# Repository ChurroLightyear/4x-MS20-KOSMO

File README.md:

# 4x MS20 KOSMO (ROUGH DRAFT)
This is a stackable but very crude MS20 filter based on the KS20 by Kassutronics

This has been tested and is working with some 100% neccesary changes

***The transitor footprints ended up backwords on Kicad.

Theres a few changes that are planned with this filter but it's up and working great atm. Everything is offboard wired from the PCBs. I drilled a custom alumunum panel and made some changes to the circuit.

The biggest change was the glaring backwords transistor footprints. This clearly will not work at all without those placed correctly. Then the cutoff, shape (lp/hp), the cv amount pots have the pad positions reversed (square pad is leg 3 not 1)
I updated the schematic and the Old gerbers to have the transitors placed correctly but double check.
I took out out r23 and added a 2k trimpot in place This adjusts the range of the throw
I changed r19 to a 47k. I was finding the CV range to be kind of dissapointing with  the original 100k.
It's not on the PCB but I added the trimpots for adjusting the scale and weight of the filter and connected the weight like a second cv knob with a trimpot and the scale adjusts the range
I also added a 6db/12db slope option like eddybergmans design https://www.eddybergman.com/2019/12/synthesizer-build-part-12-korg-ms20.html
The trimpots are in the schematic but for the 6db/12db option follow the schematic I'll update it in the future
The Ms20 new is for a future plan with using 90 degree headers and adding a jack panel and a pot panel with angled holes for the trimpots.
!!!theres no protection diodes on this circuit
for a single filter you may be able to get away without adding the trimpots but the variability in the filters are far too great.
I used bc558s instead of 557s like kassutronics also and I've heard you should match them but I didn't and it came out fine

The files I used are in the OLD folders and the new folders a future (probably a good bit from now) plan

The new PCBs will have a Panel, control PCB, jacks pcb, and 4 filter stacks on each. The resistor values will be where I found to like them. There will be 2 90 degree mounted adjustment trimpots. Switches for the 12db, 6db shelfs. 4 sets of 90 degree header pins to attach the pcbs to the main board. 1 filter knob, 2 dpdt (on/on) switches for the shelf (filters 1/2 and 3/4), 2 stereo pots (resonance 1/2 and 3/4) 4 cv level pots, 4 lp/hp mix pot, 4 drive pots, 4 input jacks, 4 output jacks and 4 cv jacks. All with no off board wiring (currently its around 100 wires) and removing the standoff holes and power header slots.

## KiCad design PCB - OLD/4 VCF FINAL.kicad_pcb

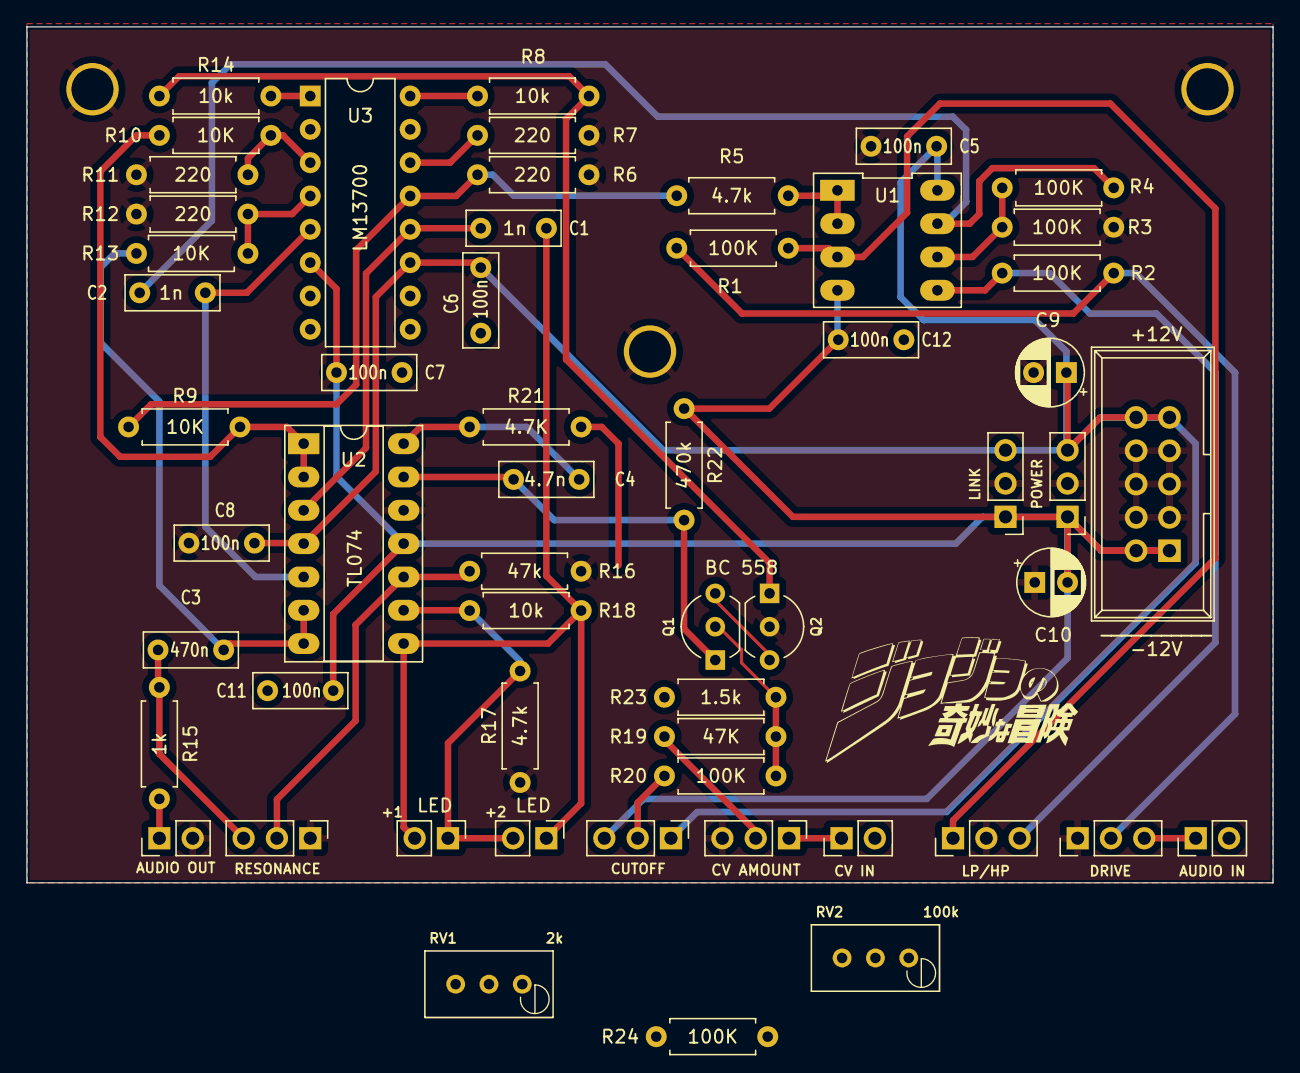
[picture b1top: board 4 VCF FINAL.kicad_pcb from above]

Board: 2 copper layers, 95.0 x 65.2 mm, 56 parts (0 on the bottom side), 31 nets.

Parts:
+1, +2: LED; PinHeader_1x02_P2.54mm_Vertical
AUDIO OUT: AUDIO OUT; PinHeader_1x02_P2.54mm_Vertical
C1, C2: 1n; BOX cap
C3: 470n; BOX cap
C4: 4.7n; BOX cap
C5, C6, C7, C8, C11, C12: 100n; BOX cap
C9, C10: 10u; Elec CAP
CUTOFF: 100K; PinHeader_1x03_P2.54mm_Vertical
DRIVE: 100K; PinHeader_1x03_P2.54mm_Vertical
J0: POWER; Power_Header
J1: AUDIO IN; PinHeader_1x02_P2.54mm_Vertical
J2: CV IN; PinHeader_1x02_P2.54mm_Vertical
LINK: POWER; PinHeader_1x03_P2.54mm_Vertical
LP/HP: 100K; PinHeader_1x03_P2.54mm_Vertical
POWER: POWER; PinHeader_1x03_P2.54mm_Vertical
Q1, Q2: TO-92_Inline_Wide
R1, R2, R3, R4, R20, R24: 100K; R
R5, R17: 4.7k; R
R6, R7, R11, R12: 220; R
R8, R14, R18: 10k; R
R9, R10, R13: 10K; R
R15: 1k; R
R16: 47k; R
R19: 47K; R
R21: 4.7K; R
R22: 470k; R
R23: 1.5k; R
RESONANCE: 100K; PinHeader_1x03_P2.54mm_Vertical
RV1: 1k; Potentiometer_Bourns_3296W_Vertical
RV2: 100k; Potentiometer_Bourns_3296W_Vertical
RV4: CV AMOUNT; PinHeader_1x03_P2.54mm_Vertical
U1: TL072
U2: TL074
U3: LM13700; DIP-16_W7.62mm

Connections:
+12V: C6.1, C7.1, C8.1, C9.1, CUTOFF.1, J0.9, J0.10, LINK.3, POWER.3, RV2.1, U1.8 (V+), U2.4 (V+), U3.11 (V+)
-12V: C5.1, C10.2, C11.1, C12.1, CUTOFF.3, J0.1, J0.2, LINK.1, POWER.1, R22.1, RV2.3, U1.4 (V-), U2.11 (V-), U3.6 (V-)
CUT: Q2.1, R8.1, R14.1
GND: AUDIO OUT.2, C5.2, C6.2, C7.2, C8.2, C9.2, C10.1, C11.2, C12.2, DRIVE.1, J0.3, J0.4, J0.5, J0.6, J0.7, J0.8, LINK.2, LP/HP.2, POWER.2, Q2.2, R3.1, R6.1, R7.1, R11.1, R12.1, R16.1, R17.1, RESONANCE.1, RV1.2, RV1.3, RV4.3, U2.12 (+)
unnamed: +1.2 (A), +2.1 (K), C1.2, R18.2, U2.8
unnamed: +1.1 (K), +2.2 (A), R17.2, R18.1, U2.9 (-)
unnamed: C2.2, R4.2, U1.7
unnamed: C3.2, R15.1, RESONANCE.3
unnamed: C4.1, R21.1, U2.14
unnamed: R1.1, R2.1
unnamed: AUDIO OUT.1, R15.2
unnamed: Q1.2, R19.2, R20.2, R23.2, R24.2
unnamed: C4.2, Q1.1, R22.2, U2.13 (-)
unnamed: Q1.3, Q2.3, R21.2
unnamed: R8.2, U3.16
unnamed: R14.2, U3.1
unnamed: R23.1, RV1.1
unnamed: R24.1, RV2.2
unnamed: R1.2, U1.3 (+)
unnamed: R5.1, U1.1, U1.2 (-)
unnamed: R2.2, U1.5 (+)
unnamed: R3.2, R4.1, U1.6 (-)
unnamed: C1.1, U2.3 (+), U3.12
unnamed: R9.2, R10.1, U2.1, U2.2 (-)
unnamed: C2.1, U2.5 (+), U3.5
unnamed: C3.1, R13.2, U2.6 (-), U2.7
unnamed: R16.2, U2.10 (+)
unnamed: R7.2, U3.14 (+)
unnamed: R5.2, R6.2, R9.1, U3.13 (-)
unnamed: R10.2, R11.2, U3.3 (+)
unnamed: R12.2, R13.1, U3.4 (-)
